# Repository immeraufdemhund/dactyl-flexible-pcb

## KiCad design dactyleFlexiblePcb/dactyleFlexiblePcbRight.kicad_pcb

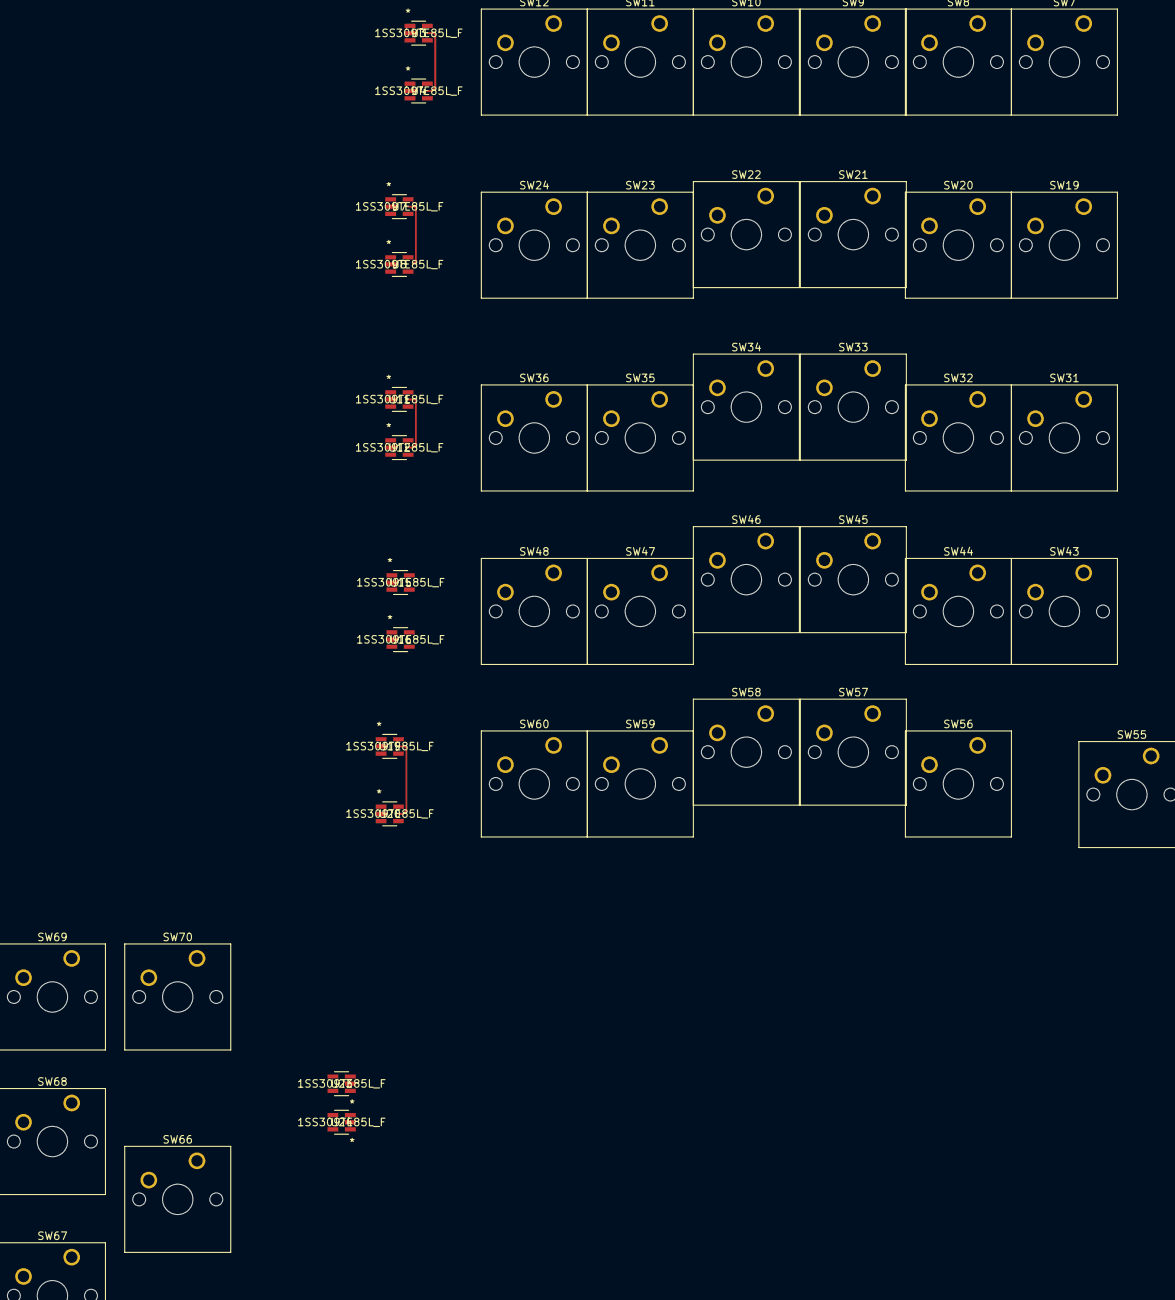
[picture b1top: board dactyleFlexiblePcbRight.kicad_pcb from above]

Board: 2 copper layers, 47 parts (0 on the bottom side), 41 nets.

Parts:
SW7, SW8, SW9, SW10, SW11, SW12, SW19, SW20, SW21, SW22, SW23, SW24, SW31, SW32, SW33, SW34, SW35, SW36, SW43, SW44, SW45, SW46, SW47, SW48, SW55, SW56, SW57, SW58, SW59, SW60, SW66, SW67, SW68, SW69, SW70: SW_MEC_5G; SW_Cherry_MX_1.00u_PCB
U3, U4, U7, U8, U11, U12, U15, U16, U19, U20, U23, U24: 1SS309TE85L_F

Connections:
B1R: U11.2, U12.2
B2R: U19.2, U20.2
B3R: U15.2, U16.2
B6R: U23.2, U24.2
F6R: U3.2, U4.2
F7R: U7.2, U8.2
unnamed: SW7.1, SW7.2, U4.3
unnamed: SW8.1, SW8.2, U3.1
unnamed: SW9.1, SW9.2, U3.5
unnamed: SW10.1, SW10.2, U3.4
unnamed: SW11.1, SW11.2, U3.3
unnamed: SW12.1, SW12.2, U4.1
unnamed: SW19.1, SW19.2, U8.3
unnamed: SW20.1, SW20.2, U7.1
unnamed: SW21.1, SW21.2, U7.5
unnamed: SW22.1, SW22.2, U7.4
unnamed: SW23.1, SW23.2, U7.3
unnamed: SW24.1, SW24.2, U8.1
unnamed: SW31.1, SW31.2, U12.3
unnamed: SW32.1, SW32.2, U11.1
unnamed: SW33.1, SW33.2, U11.5
unnamed: SW34.1, SW34.2, U11.4
unnamed: SW35.1, SW35.2, U11.3
unnamed: SW36.1, SW36.2, U12.1
unnamed: SW43.1, SW43.2, U16.3
unnamed: SW44.1, SW44.2, U15.1
unnamed: SW45.1, SW45.2, U15.5
unnamed: SW46.1, SW46.2, U15.4
unnamed: SW47.1, SW47.2, U15.3
unnamed: SW48.1, SW48.2, U16.1
unnamed: SW55.1, SW55.2, U20.3
unnamed: SW56.1, SW56.2, U19.1
unnamed: SW57.1, SW57.2, U19.5
unnamed: SW58.1, SW58.2, U19.4
unnamed: SW59.1, SW59.2, U19.3
unnamed: SW60.1, SW60.2, U20.1
unnamed: SW66.1, SW66.2, U24.3
unnamed: SW67.1, SW67.2, U23.1
unnamed: SW68.1, SW68.2, U23.5
unnamed: SW69.1, SW69.2, U23.4
unnamed: SW70.1, SW70.2, U23.3

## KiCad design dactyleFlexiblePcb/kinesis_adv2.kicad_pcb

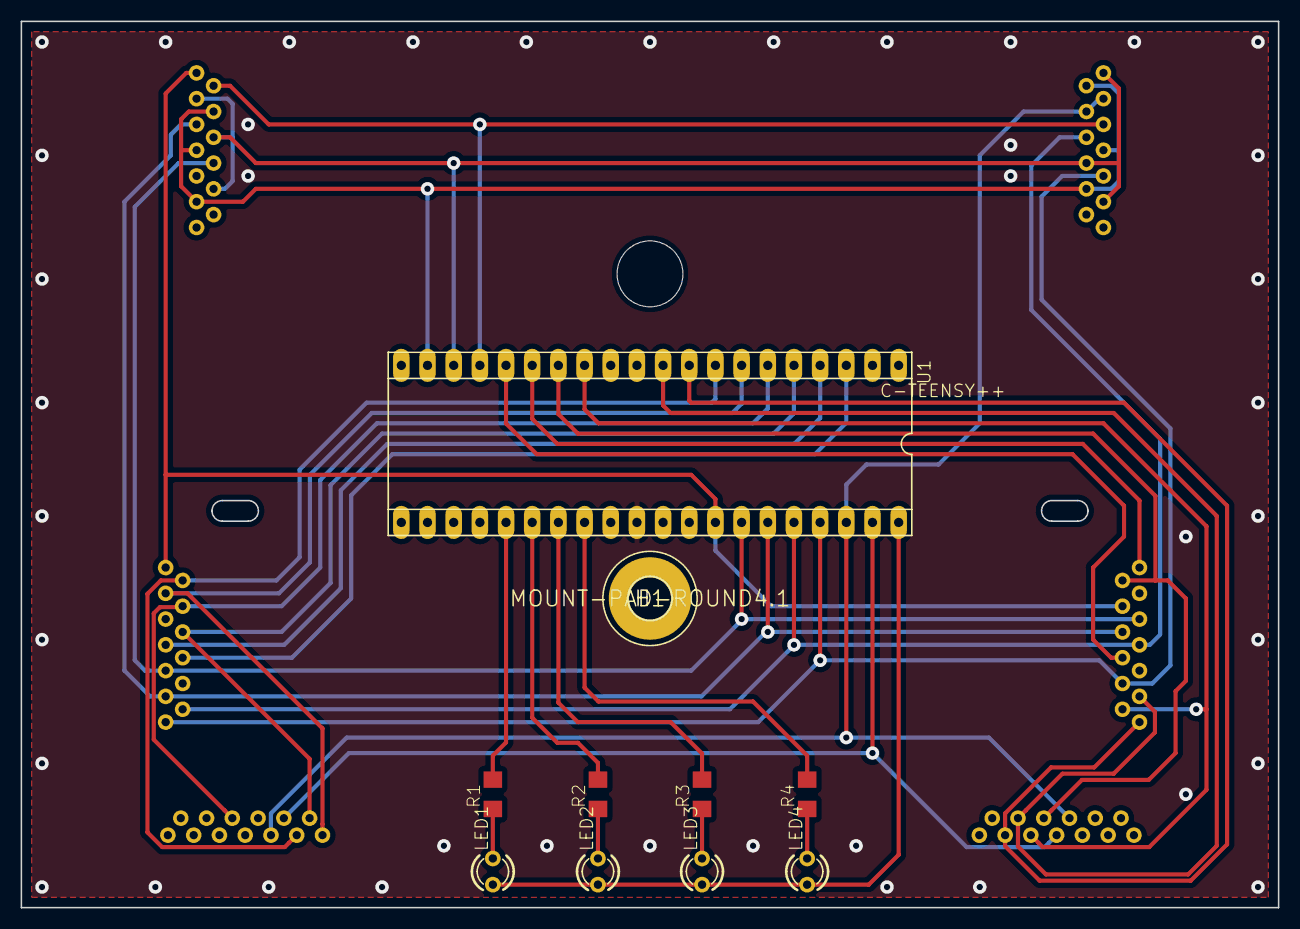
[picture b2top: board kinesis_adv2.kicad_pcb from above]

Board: 16 copper layers, 122.0 x 86.0 mm, 17 parts (0 on the bottom side), 31 nets.

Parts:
@HOLE0: (no value)
H1: MOUNT-PAD-ROUND4.1; 4,1-PAD
LED1, LED2, LED3, LED4: LED3MM
R1, R2, R3, R4: R1206
TASTENLINKS: 39-53-2355; 39-53-2135
TASTENLINKS#2, TASTENLINKS#3: 39-53-2355; 39-53-2135
TASTENRECHTS: 39-53-2355; 39-53-2135
TOPLINKS: 39-53-2355; 39-53-2135
TOPRECHTS: 39-53-2355; 39-53-2135
U1: C-TEENSY++; TEENSY++

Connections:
B0: TASTENLINKS.P$1, TASTENRECHTS.P$10, TOPLINKS.P$1, U1.B0
B1: TASTENLINKS.P$9, TASTENRECHTS.P$9, TOPLINKS.P$8, U1.B1
B2: TASTENLINKS.P$11, TASTENRECHTS.P$8, TOPLINKS.P$5, U1.B2
B3: TASTENLINKS.P$12, TASTENRECHTS.P$7, TOPRECHTS.P$8, U1.B3
B4: TASTENLINKS.P$13, TASTENRECHTS.P$4, TOPRECHTS.P$5, U1.B4
B5: TASTENLINKS#2.P$9, TASTENLINKS#3.P$8, TOPRECHTS.P$10, TOPRECHTS.P$11, U1.B5
B6: TASTENLINKS#2.P$10, TASTENLINKS#3.P$7, U1.B6
C0: TASTENLINKS#3.P$5, TASTENRECHTS.P$2, U1.C0
C1: TASTENLINKS#3.P$6, TASTENRECHTS.P$12, U1.C1
C2: TASTENRECHTS.P$13, U1.C2
C3: TASTENRECHTS.P$6, U1.C3
C4: TOPLINKS.P$2, TOPRECHTS.P$9, U1.C4
C5: TOPLINKS.P$3, TOPLINKS.P$6, TOPLINKS.P$10, TOPRECHTS.P$3, TOPRECHTS.P$6, TOPRECHTS.P$13, U1.C5
C6: TOPLINKS.P$4, TOPLINKS.P$7, TOPLINKS.P$11, TOPRECHTS.P$4, TOPRECHTS.P$7, TOPRECHTS.P$12, U1.C6
D0: TASTENLINKS.P$8, U1.D0
D1: TASTENLINKS.P$7, U1.D1
D2: TASTENLINKS.P$6, TASTENLINKS#2.P$12, U1.D2
D3: TASTENLINKS.P$4, TASTENLINKS#2.P$6, U1.D3
D4: TASTENLINKS.P$3, TASTENLINKS#2.P$13, U1.D4
D5: TASTENLINKS.P$2, TASTENLINKS#2.P$11, U1.D5
D6: TASTENLINKS#3.P$3, TASTENRECHTS.P$1, U1.D6
D7: TASTENLINKS#3.P$4, TASTENRECHTS.P$3, U1.D7
unnamed: R1.2, U1.F3
unnamed: R2.2, U1.F2
unnamed: R3.2, U1.F1
unnamed: R4.2, U1.F0
unnamed: LED1.A, LED2.A, LED3.A, LED4.A, U1.+5V
unnamed: LED4.K, R4.1
unnamed: LED3.K, R3.1
unnamed: LED2.K, R2.1
unnamed: LED1.K, R1.1

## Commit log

2020-06-25 initial project import
2020-06-25 add 2 1SS309 to the schematic randomly. No idea what i'm doing yet
2020-08-01 I have no idea what to commit :D

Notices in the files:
parts and their libraries:
Copyright 2016 Accelerated Designs. All rights reserved.
